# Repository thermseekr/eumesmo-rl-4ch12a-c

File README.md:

# eumesmo-rl-4ch12a-c

Relay board with 4x 24 VDC Form C (NO + NC) relays. This board is designed to be used togheter with [eumesmo-io-24v16ch](https://github.com/thermseekr/eumesmo-io-24v16ch), but can be driven by any 24V control circuit compatible with NPN inputs. It uses 16A relays and is limited to 12A/channel per copper trace capacity.

The board is compatible with the SP7 DIN rail system from Metaltex.

## VERSION HISTORY

V1.3 - 2026/09/21 - Repository renamed from eumesmo-rl-4ch12A-nc to eumesmo-rl-4ch12A-c to reflect the change on the relay contact form.

V1.2 - 2026/06/13 - Repository renamed from RELAY-24V-4CH-12A-NC to eumesmo-rl-4ch12A-nc to align the design with the eumesmo line of building automation products.

V1.1 - 2026/06/13 - Input terminal blocks replaced from 2.54mm to 3.5mm pitch for easier installation in the field.

V1.0 - Initial release.

## LICENSE

This project is licensed under the [Creative Commons BY-NC 4.0 License](https://creativecommons.org/licenses/by-nc/4.0/).
Commercial use is not permitted without prior written consent. See the [LICENSE.txt](LICENSE.txt) file for details.

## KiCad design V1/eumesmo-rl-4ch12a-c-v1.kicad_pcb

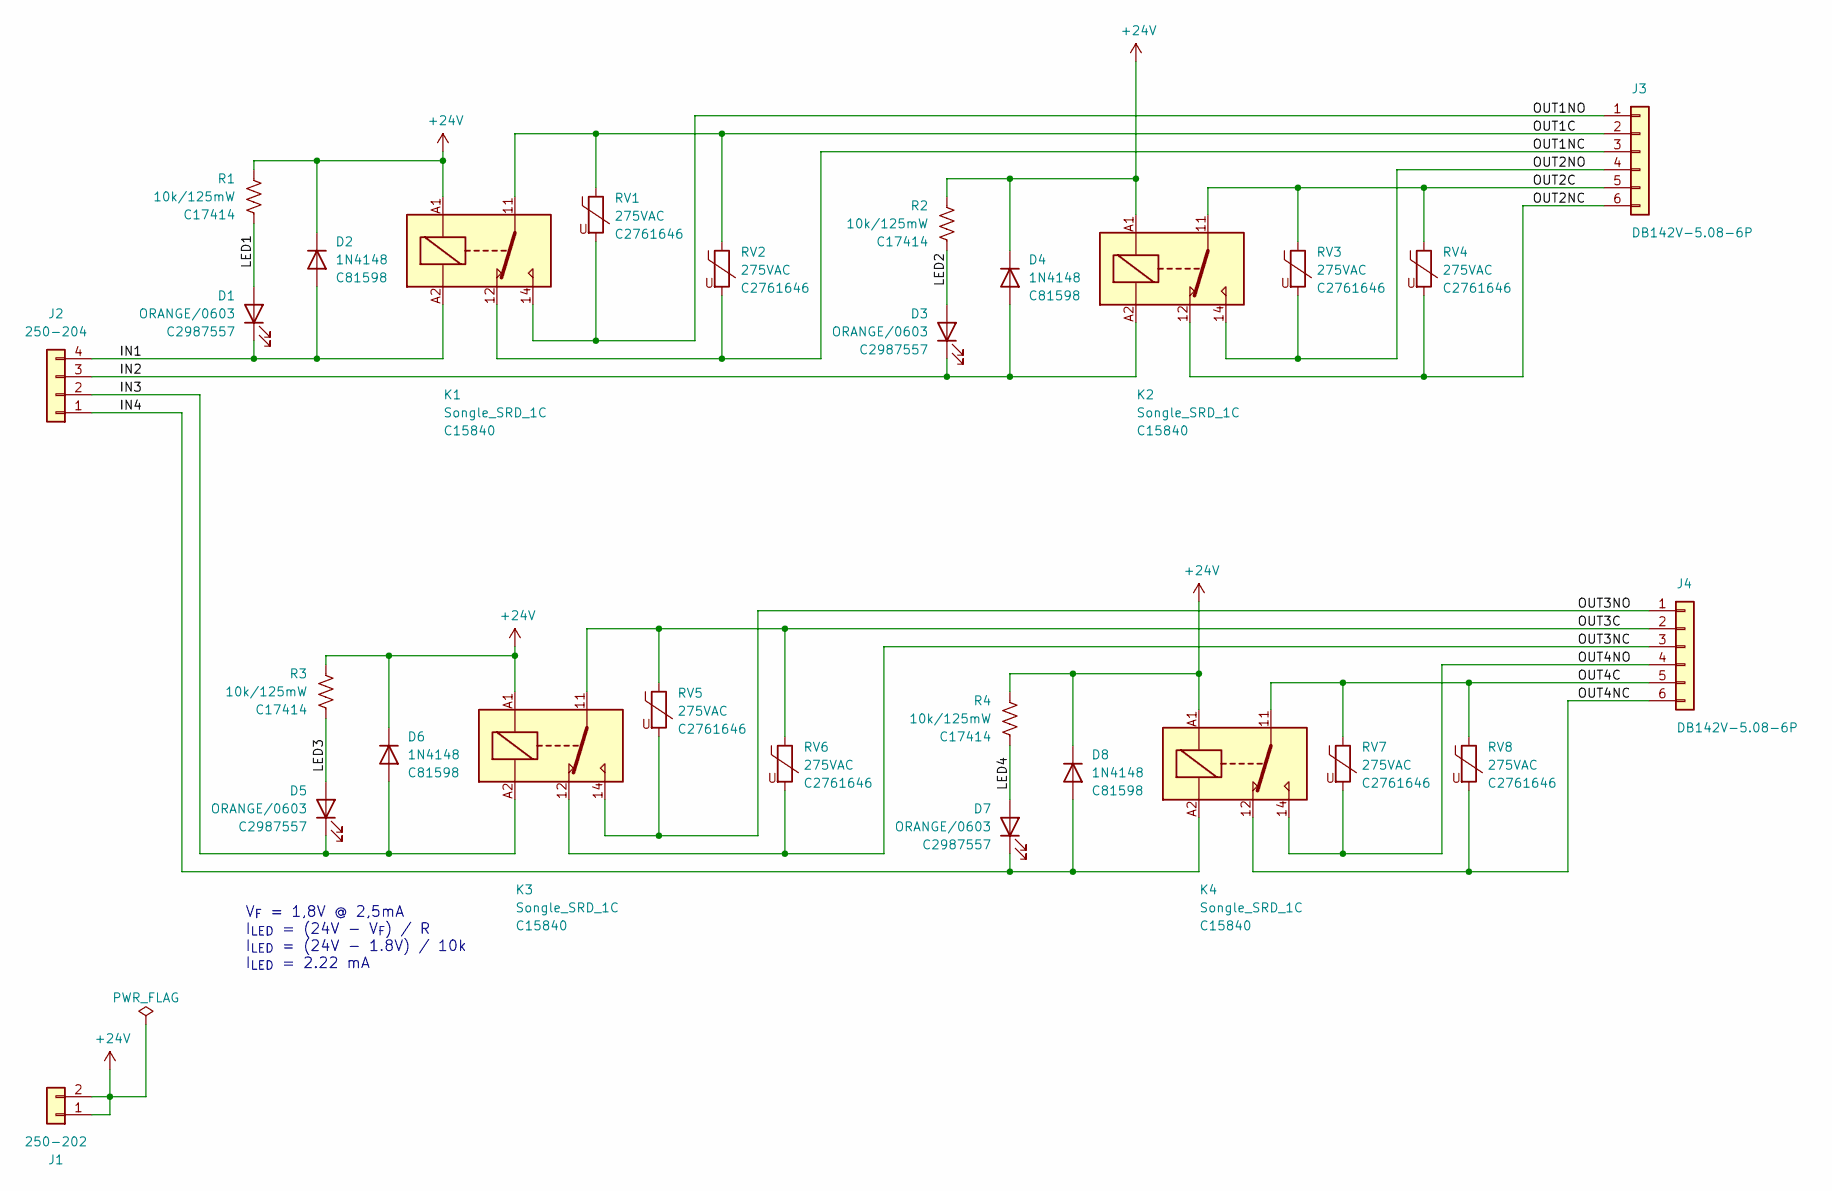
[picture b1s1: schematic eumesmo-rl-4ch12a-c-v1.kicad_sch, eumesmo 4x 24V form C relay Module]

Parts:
D1, D3, D5, D7: ORANGE/0603; LED_0603_1608Metric; Mfr PN 19-217/S2C-AL1M2VY/6T; LCSC Part # C2987557
D2, D4, D6, D8: 1N4148; D_SOD-123; Mfr PN 1N4148W; LCSC Part # C81598
J1: 250-202; TerminalBlock_Wago_250-202_1x02_P3.5mm_45Degree; Mfr PN KF250-3.5-2P-1; LCSC Part # C475154
J2: 250-204; TerminalBlock_Wago_250-204_1x04_P3.5mm_45Degree; Mfr PN KF250-3.5-4P-1; LCSC Part # C475156
J3, J4: DB142V-5.08-6P; TerminalBlock_Dibo_DB142V-5.08-6P_1x06_P5.08mm_Vertical; Mfr PN DB142V-5.08-6P-GN; LCSC Part # C2898703
K1, K2, K3, K4: Songle_SRD_1C; Relay_SPDT_Songle_SRD_FormC; Mfr PN SRD-24VDC-SL-C; LCSC Part # C15840
R1, R2, R3, R4: 10k/125mW; R_0805_2012Metric; Mfr PN 0805W8F1002T5E; LCSC Part # C17414
RV1, RV2, RV3, RV4, RV5, RV6, RV7, RV8: 275VAC; RV_Disc_D9.50mm_W3.6mm_P5.08mm; Mfr PN RM07D431KC1IE100; LCSC Part # C2761646

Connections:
+24V: D2.1 (K), D4.1 (K), D6.1 (K), D8.1 (K), J1.1, J1.2, K1.A1, K2.A1, K3.A1, K4.A1, R1.1, R2.1, R3.1, R4.1
/IN1: D1.1 (K), D2.2 (A), J2.4, K1.A2
/IN2: D3.1 (K), D4.2 (A), J2.3, K2.A2
/IN3: D5.1 (K), D6.2 (A), J2.2, K3.A2
/IN4: D7.1 (K), D8.2 (A), J2.1, K4.A2
/LED1: D1.2 (A), R1.2
/LED2: D3.2 (A), R2.2
/LED3: D5.2 (A), R3.2
/LED4: D7.2 (A), R4.2
/OUT1C: J3.2, K1.11, RV1.1, RV2.1
/OUT1NC: J3.3, K1.12, RV2.2
/OUT1NO: J3.1, K1.14, RV1.2
/OUT2C: J3.5, K2.11, RV3.1, RV4.1
/OUT2NC: J3.6, K2.12, RV4.2
/OUT2NO: J3.4, K2.14, RV3.2
/OUT3C: J4.2, K3.11, RV5.1, RV6.1
/OUT3NC: J4.3, K3.12, RV6.2
/OUT3NO: J4.1, K3.14, RV5.2
/OUT4C: J4.5, K4.11, RV7.1, RV8.1
/OUT4NC: J4.6, K4.12, RV8.2
/OUT4NO: J4.4, K4.14, RV7.2

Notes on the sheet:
V_{F} = 1,8V @ 2,5mA I_{LED} = (24V - V_{F}) / R I_{LED} = (24V - 1.8V) / 10k I_{LED} = 2.22 mA

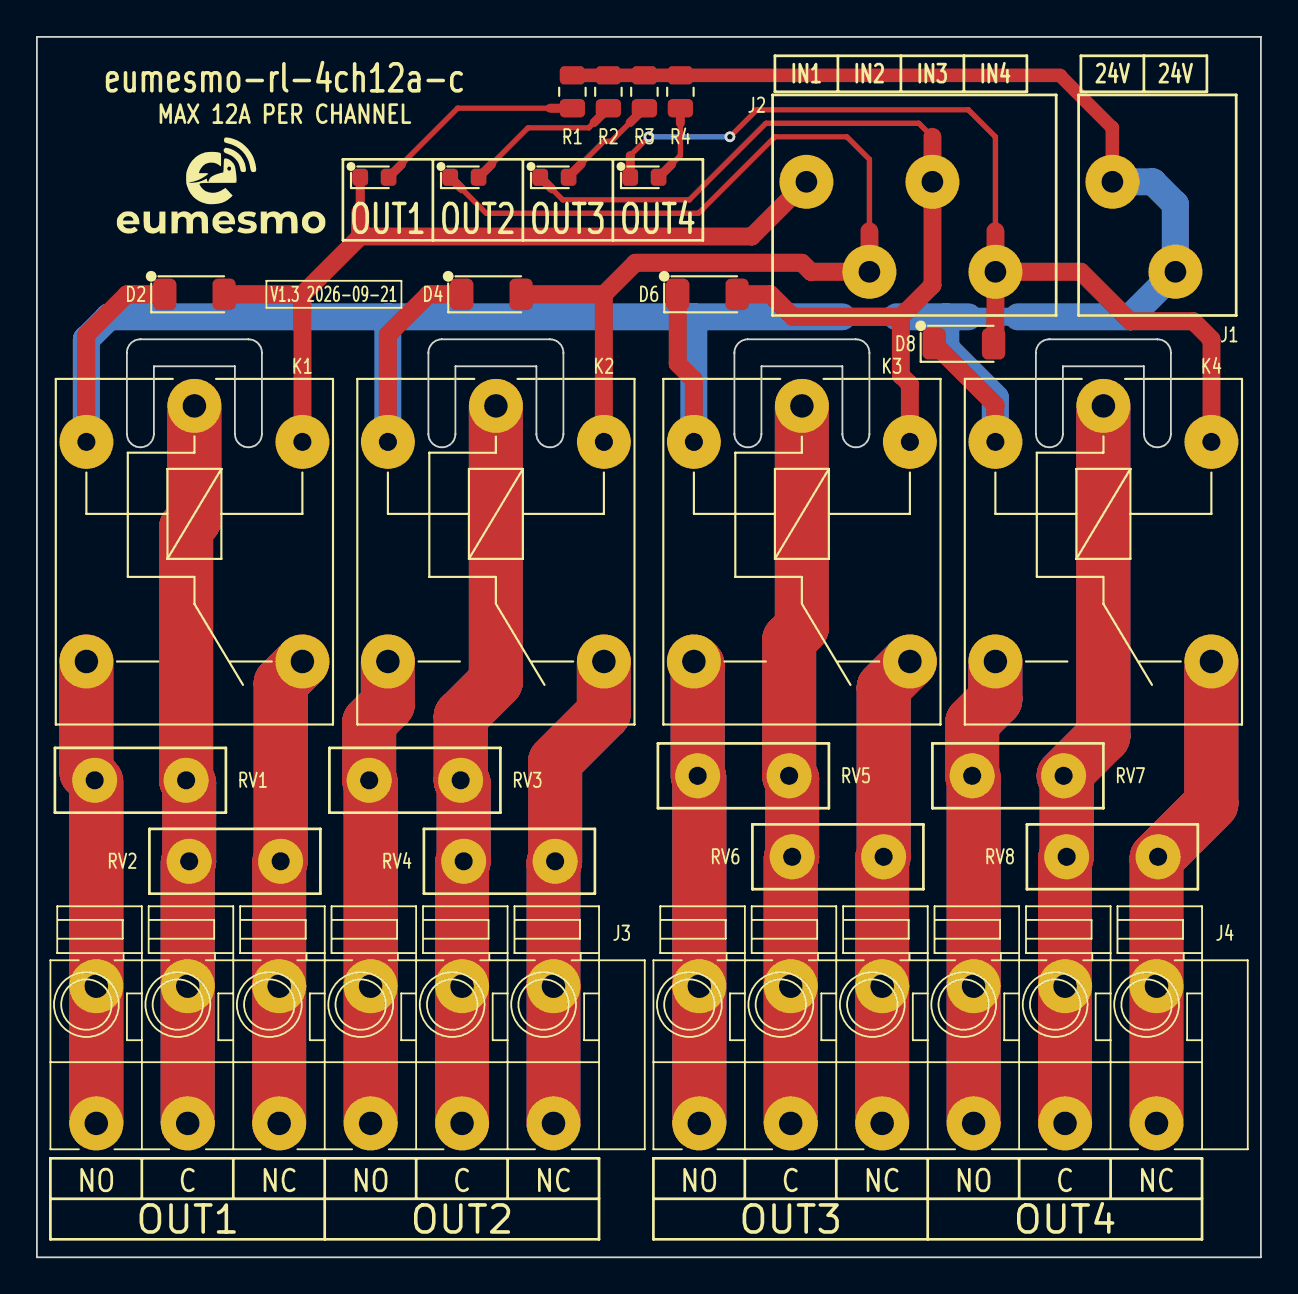
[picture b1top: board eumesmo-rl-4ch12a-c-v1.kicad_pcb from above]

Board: 2 copper layers, 68.0 x 67.8 mm, 28 parts (0 on the bottom side), 21 nets.

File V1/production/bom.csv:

Designator,Footprint,Quantity,Value,LCSC Part #
"D1, D3, D5, D7",0603,4,ORANGE/0603,C2987557
"D2, D4, D6, D8",D_SOD-123,4,1N4148,C81598
J1,TerminalBlock_Wago_250-202_1x02_P3.5mm_45Degree,1,250-202,C475154
J2,TerminalBlock_Wago_250-204_1x04_P3.5mm_45Degree,1,250-204,C475156
"J3, J4",TerminalBlock_Dibo_DB142V-5.08-6P_1x06_P5.08mm_Vertical,2,DB142V-5.08-6P,C2898703
"K1, K2, K3, K4",Relay_SPDT_Songle_SRD_FormC,4,Songle_SRD_1C,C15840
"R1, R2, R3, R4",0805,4,10k/125mW,C17414
"RV1, RV2, RV3, RV4, RV5, RV6, RV7, RV8",RV_Disc_D9.50mm_W3.6mm_P5.08mm,8,275VAC,C2761646
